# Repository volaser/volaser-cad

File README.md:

# volaser-cad
CAD files and assembly instructions to create your very own volaser

## Assembly
Assembly instructions are detailed step by step in the [wiki](https://github.com/volaser/volaser-cad/wiki)

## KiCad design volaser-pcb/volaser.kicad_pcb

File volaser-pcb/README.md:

# Volaser PCB

The Volaser PCB connects the Sparkfun ESP32 microcontroller board which the servo motor controller and two lasers. It also hosts a 5V voltage regulator for the laser modules and a 3.3V regulator for the microcontroller and stepper motor driver. To make your own, send the gerber files to any PCB fabrication facility (an easy one to use is https://jlcpcb.com/).

- [Schematic](images/volaser_schematic.pdf)
- [PCB layout](images/volaser_pcb.pdf)

For assembly instructions look on the [wiki](https://github.com/volaser/volaser-cad/wiki/Volaser-PCB-Assembly).

The finished PCB should look something like this

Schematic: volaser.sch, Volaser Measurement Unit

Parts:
A1: Pololu_Breakout_A4988; Pololu_Breakout-16_15.2x20.3mm
BT1: Battery; JST_XH_B02B-XH-A_1x02_P2.54mm_Vertical
C1: 0.33uF; CP_Radial_D5.0mm_P2.00mm
C2: 0.1uF; CP_Radial_D5.0mm_P2.00mm
C3, C4: 10uF; CP_Radial_D5.0mm_P2.00mm
C5, C6: 100uF; CP_Radial_D8.0mm_P3.50mm
H1, H2, H3, H4: MountingHole; MountingHole_4.3mm_M4
H5, H6: MountingHole; MountingHole_2.7mm_M2.5
J1, J2: Conn_01x04; JST_XH_B04B-XH-A_1x04_P2.54mm_Vertical
J3: Conn_01x06; JST_XH_B06B-XH-A_1x06_P2.54mm_Vertical
J4: Barrel_Jack_Switch; BarrelJack_Horizontal
L1, L2: tf-mini; Hirose_DF13-04P-1.25DSA_1x04_P1.25mm_Vertical
M1: Stepper_Motor_bipolar; JST_XH_B04B-XH-A_1x04_P2.54mm_Vertical
Q1: IRLB8721; TO-220F-3_Horizontal_TabDown
S1: slipring; JST_XH_B06B-XH-A_1x06_P2.54mm_Vertical
SW1: SW_SPST; JST_XH_B02B-XH-A_1x02_P2.54mm_Vertical
U1: LM7805; TO-220F-3_Horizontal_TabDown
U2: LM1117-3.3; TO-220F-3_Horizontal_TabDown
U3: Sparkfun_ESP32

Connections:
+3V3: A1.2 (VDD), C4.1, U2.2 (VO), U3.5
+5V: C2.1, J1.2, J2.2, J3.1, L1.2, L2.2, S1.1, U1.3 (VO)
+BATT: A1.8 (VMOT), C1.2, C3.1, C5.1, Q1.3 (S), U1.1 (VI), U2.3 (VI)
/DIR: A1.16 (DIR), U3.16
/LaserH_RX: J2.3, J3.5, L2.3, S1.5, U3.8
/LaserH_TX: J2.4, J3.6, L2.4, S1.6, U3.7
/LaserV_RX: J1.3, J3.3, L1.3, S1.3, U3.10
/LaserV_TX: J1.4, J3.4, L1.4, S1.4, U3.9
/MS1: A1.10 (MS1), U3.12
/MS2: A1.11 (MS2), U3.13
/MS3: A1.12 (MS3), U3.14
/STEP: A1.15 (STEP), U3.15
/~ENABLE: A1.9 (~ENABLE), U3.11
GND: A1.1 (GND), A1.7 (GND), BT1.2 (-), C1.1, C2.2, C3.2, C4.2, C5.2, C6.2, J1.1, J2.1, J3.2, J4.2, L1.1, L2.1, Q1.1 (G), S1.2, U1.2 (GND), U2.1 (GND), U3.1, U3.4
unnamed: A1.3 (1B), M1.1
unnamed: A1.4 (1A), M1.2 (-)
unnamed: A1.5 (2A), M1.3
unnamed: A1.6 (2B), M1.4
unnamed: A1.13 (~RESET), A1.14 (~SLEEP)
unnamed: BT1.1 (+), C6.1, J4.1, SW1.1 (A)
unnamed: Q1.2 (D), SW1.2 (B)

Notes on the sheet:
The Sparkfun variant of the ESP32 microcontroller is used here. This microcontroller supports remappable pins, and only one row of pins is used. Any ESP32 dev board can be used instead, but care should be taken to map the physical pins on the board to the communication lines on the PCB.
The Pololu breakout board for the

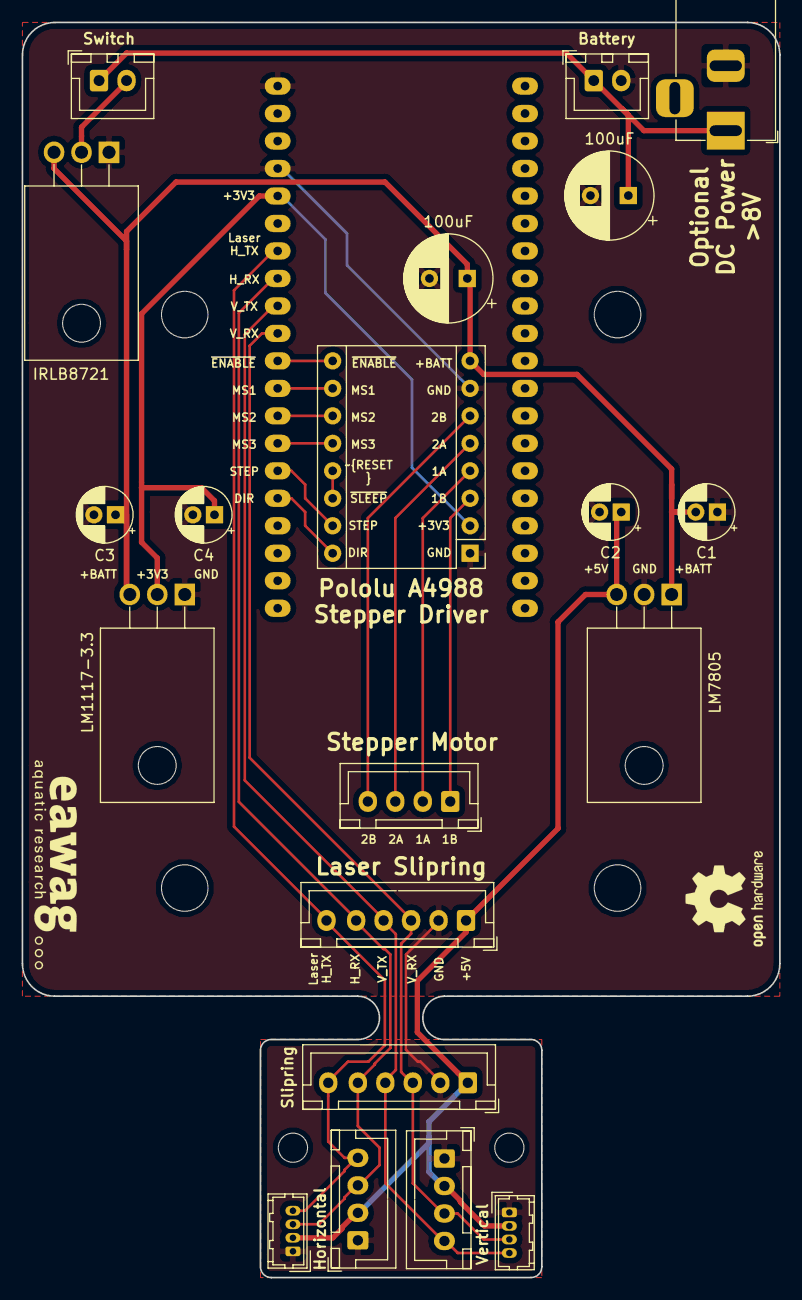
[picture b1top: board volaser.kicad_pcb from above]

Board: 2 copper layers, 70.0 x 116.0 mm, 27 parts (1 on the bottom side), 21 nets.

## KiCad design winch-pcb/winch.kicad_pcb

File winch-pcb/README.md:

# Winch PCB

The Winch PCB connects the Sparkfun ESP32 microcontroller board with the motor controller, and also hosts a voltage regulator, as well as reverse polarity protection. To make your own, send the gerber files to any PCB fabrication facility (an easy one to use is https://jlcpcb.com/).

- [Schematic](images/winch_schematic.pdf)
- [PCB layout](images/winch_pcb.pdf)

For assembly instructions look on the [wiki](https://github.com/volaser/volaser-cad/wiki/Winch-PCB-Assembly).

The finished PCB should look something like this

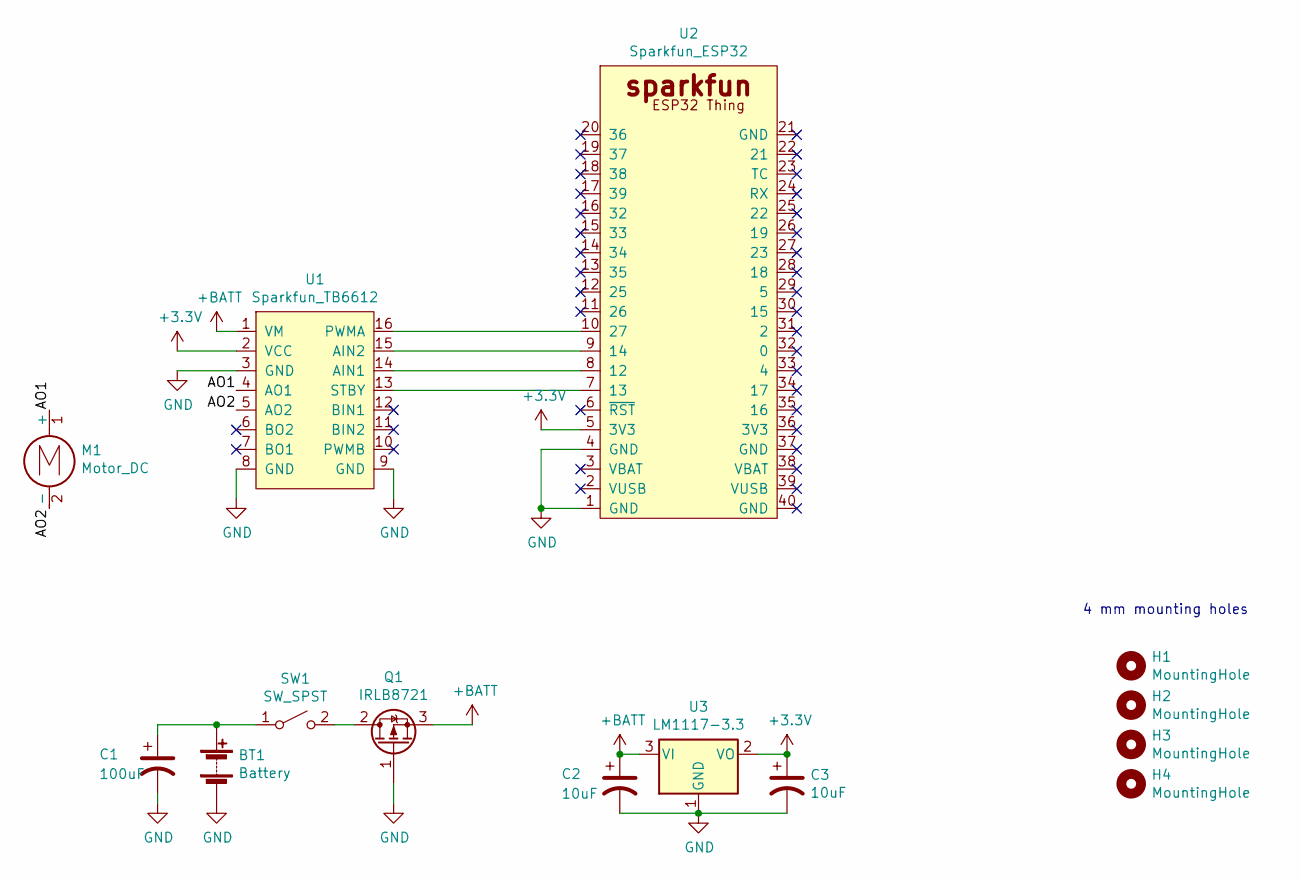
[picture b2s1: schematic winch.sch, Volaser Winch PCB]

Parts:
BT1: Battery; JST_XH_B02B-XH-A_1x02_P2.54mm_Vertical
C1: 100uF; CP_Radial_D8.0mm_P5.00mm
C2, C3: 10uF; CP_Radial_D5.0mm_P2.00mm
H1, H2, H3, H4: MountingHole; MountingHole_4mm
M1: Motor_DC; JST_XH_B02B-XH-A_1x02_P2.54mm_Vertical
Q1: IRLB8721; TO-220F-3_Horizontal_TabDown
SW1: SW_SPST; JST_XH_B02B-XH-A_1x02_P2.54mm_Vertical
U1: Sparkfun_TB6612; TB6612
U2: Sparkfun_ESP32
U3: LM1117-3.3; TO-220F-3_Horizontal_TabDown

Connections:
+3V3: C3.1, U1.2 (VCC), U2.5 (3V3), U3.2 (VO)
+BATT: C2.1, Q1.3 (S), U1.1 (VM), U3.3 (VI)
/AO1: M1.1 (+), U1.4 (AO1)
/AO2: M1.2 (-), U1.5 (AO2)
GND: BT1.2 (-), C1.2, C2.2, C3.2, Q1.1 (G), U1.3 (GND), U1.8 (GND), U1.9 (GND), U2.1 (GND), U2.4 (GND), U3.1 (GND)
unnamed: BT1.1 (+), C1.1, SW1.1 (A)
unnamed: Q1.2 (D), SW1.2 (B)
unnamed: U1.13 (STBY), U2.7 (13)
unnamed: U1.14 (AIN1), U2.8 (12)
unnamed: U1.15 (AIN2), U2.9 (14)
unnamed: U1.16 (PWMA), U2.10 (27)

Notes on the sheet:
4 mm mounting holes

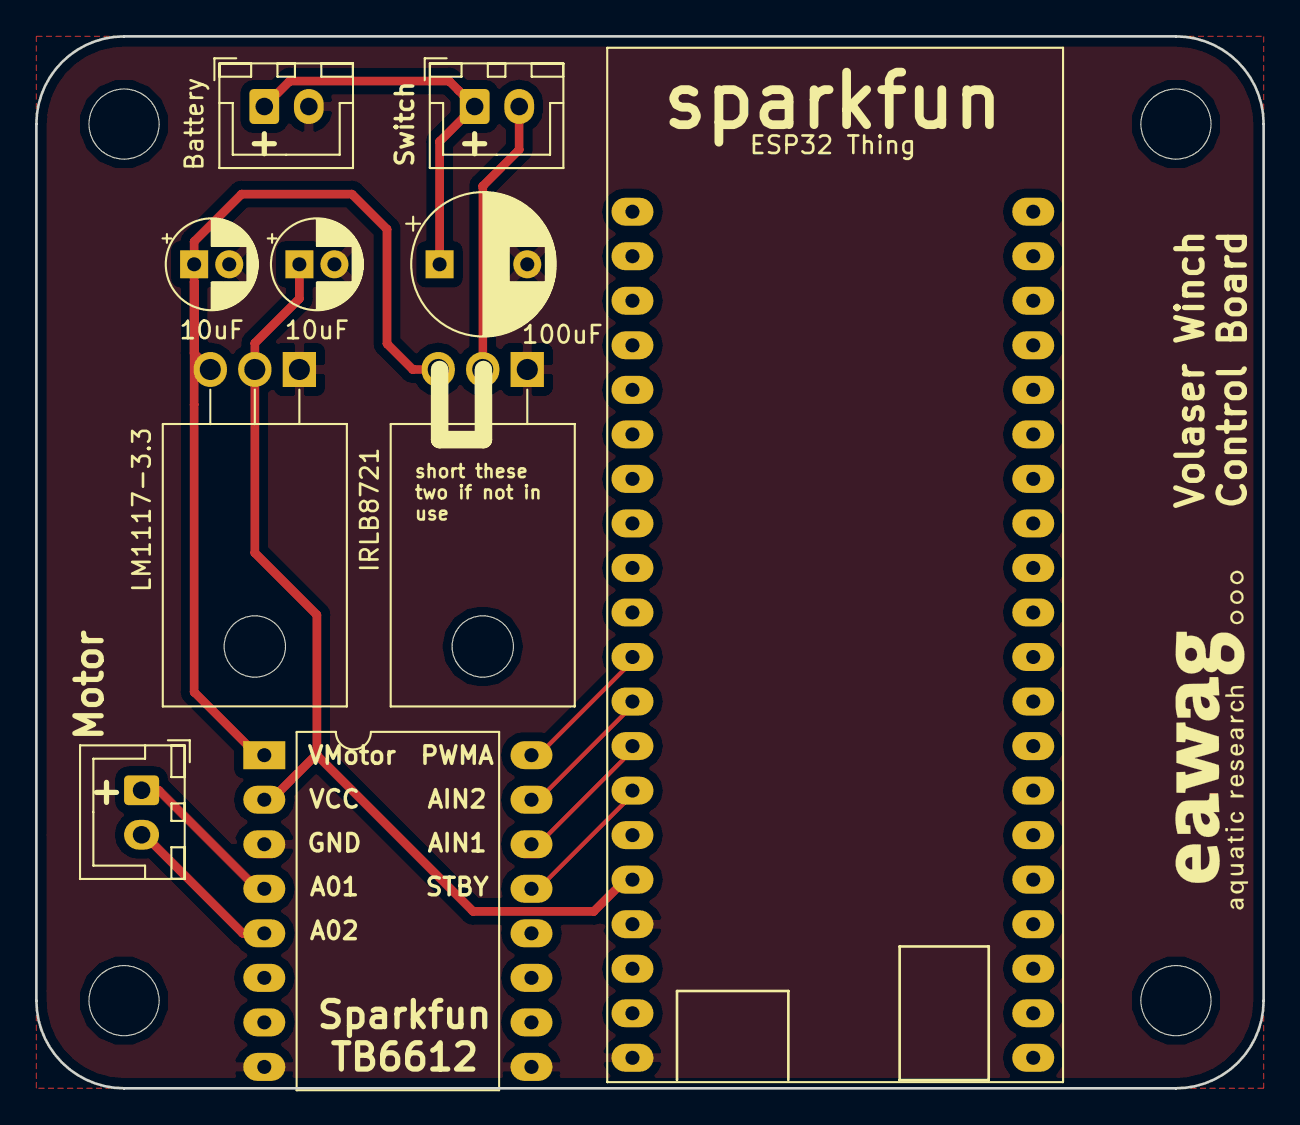
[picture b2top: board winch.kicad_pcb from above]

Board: 2 copper layers, 70.0 x 60.0 mm, 14 parts (0 on the bottom side), 11 nets.

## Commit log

2019-01-12 added PCB and CAD files
2019-01-21 replaced lower housing with part from Clara on 01.12.18, should fit the tripod
2019-01-21 fixed bad previous commit, winch lower housing now in correct place, volaser lower housing restored
2019-01-24 added images for wiki
2019-01-28 added pictures for assembly
2019-01-28 created pdfs and pngs of schmatic and board
2019-01-31 add a finished picture of the winch PCB
2019-01-31 updated winch readme
2019-01-31 fixed typo
2019-01-31 added a readme to volaser-pcb
